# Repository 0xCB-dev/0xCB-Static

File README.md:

# 0xcb-static
## 40% with OLED and Encoder running QMK

Licence | OSHWA
:-------------------------:|:-------------------------:
 | 

#### Flashing

* `qmk clone`
* `cd qmk_firmware`
* `export LTO=Y`
* To go to bootloader hold the ESC key while plugging in (or RESET switch, then hold the BOOT switch, release RESET, release BOOT).
The board should now appear in lsusb (or device manager).
* `make 0xcb/static:via:flash`

### Assembly:

You can use the [humanpnp](https://files.0xcb.dev/0xCB-Static/humanpnp.html) to easily place components.

### PCB:
KiCad 6 stable

[Schematic](https://github.com/0xCB-dev/0xcb-static/blob/main/rev1.0/0xcb-static.pdf)

Top | Bottom
:-------------------------:|:-------------------------:
  |  

### 3D files:
[STLs](https://github.com/0xCB-dev/0xcb-static/tree/main/3D-files)

#### BOM:
| References     | Value          | Quantity |Part Nb.             |
|----------------|----------------|----------|---------------------|
| C3, C4         | 20pF           | 2        |C415398              |
| C1, C2         | 0.1uF          | 2        |C409821              |
| R1, R2         | 5.1K           | 2        |C58676               |
| R3, R4         | 75             | 2        |C713897              |
| R5             | 10k            | 1        |C58673               |
| R6             | 1.5k           | 1        |C433494              |
| D1, ..., D48   | 1N4148         | 48       |C14516               |
| D49, D50       | 1N4729         | 2        |C2532                |
| U1             | ATmega328-P    | 1        |ATMEGA328P-PU-ND     |
| Y1             | 16MHz          | 1        |C16212               |
| F1             | 500mA          | 1        |C268799              |
| SW1, SW2       | RESET, BOOT    | 1        |450-1650-ND          |
| MX1, ..., MX44 | MX-NoLED       | 43       |Cherry MX switches   |
| OL1            | OLED           | 1        |SSD1306 128x32       |
| MX12           | EC11           | 1        |PEC11R-4220F-S0024-ND|
| J1             | USB4085 Type C | 1        |640-USB4085-GF-A     |

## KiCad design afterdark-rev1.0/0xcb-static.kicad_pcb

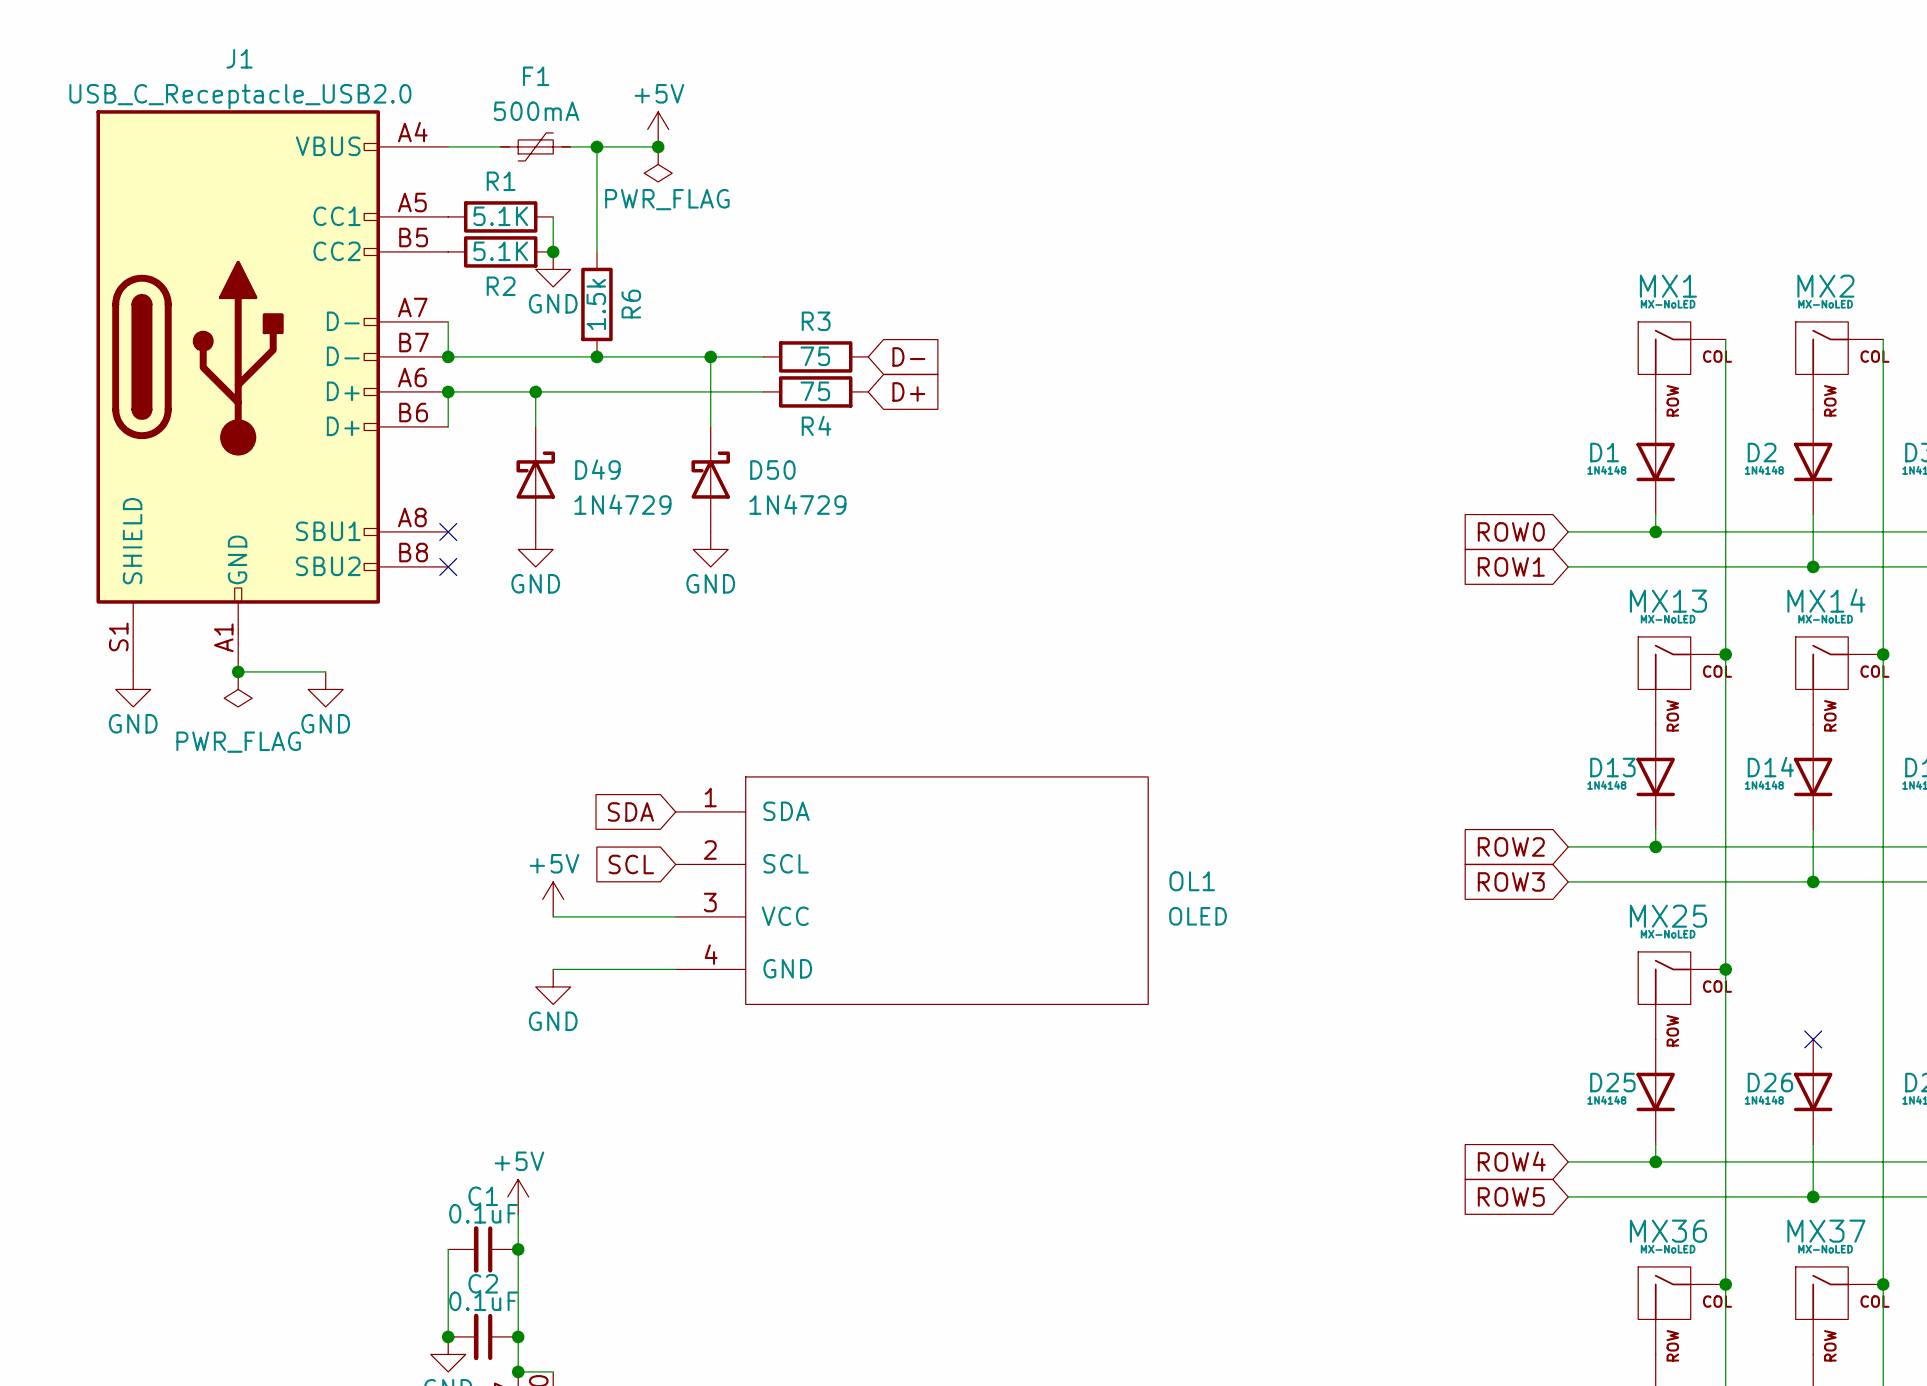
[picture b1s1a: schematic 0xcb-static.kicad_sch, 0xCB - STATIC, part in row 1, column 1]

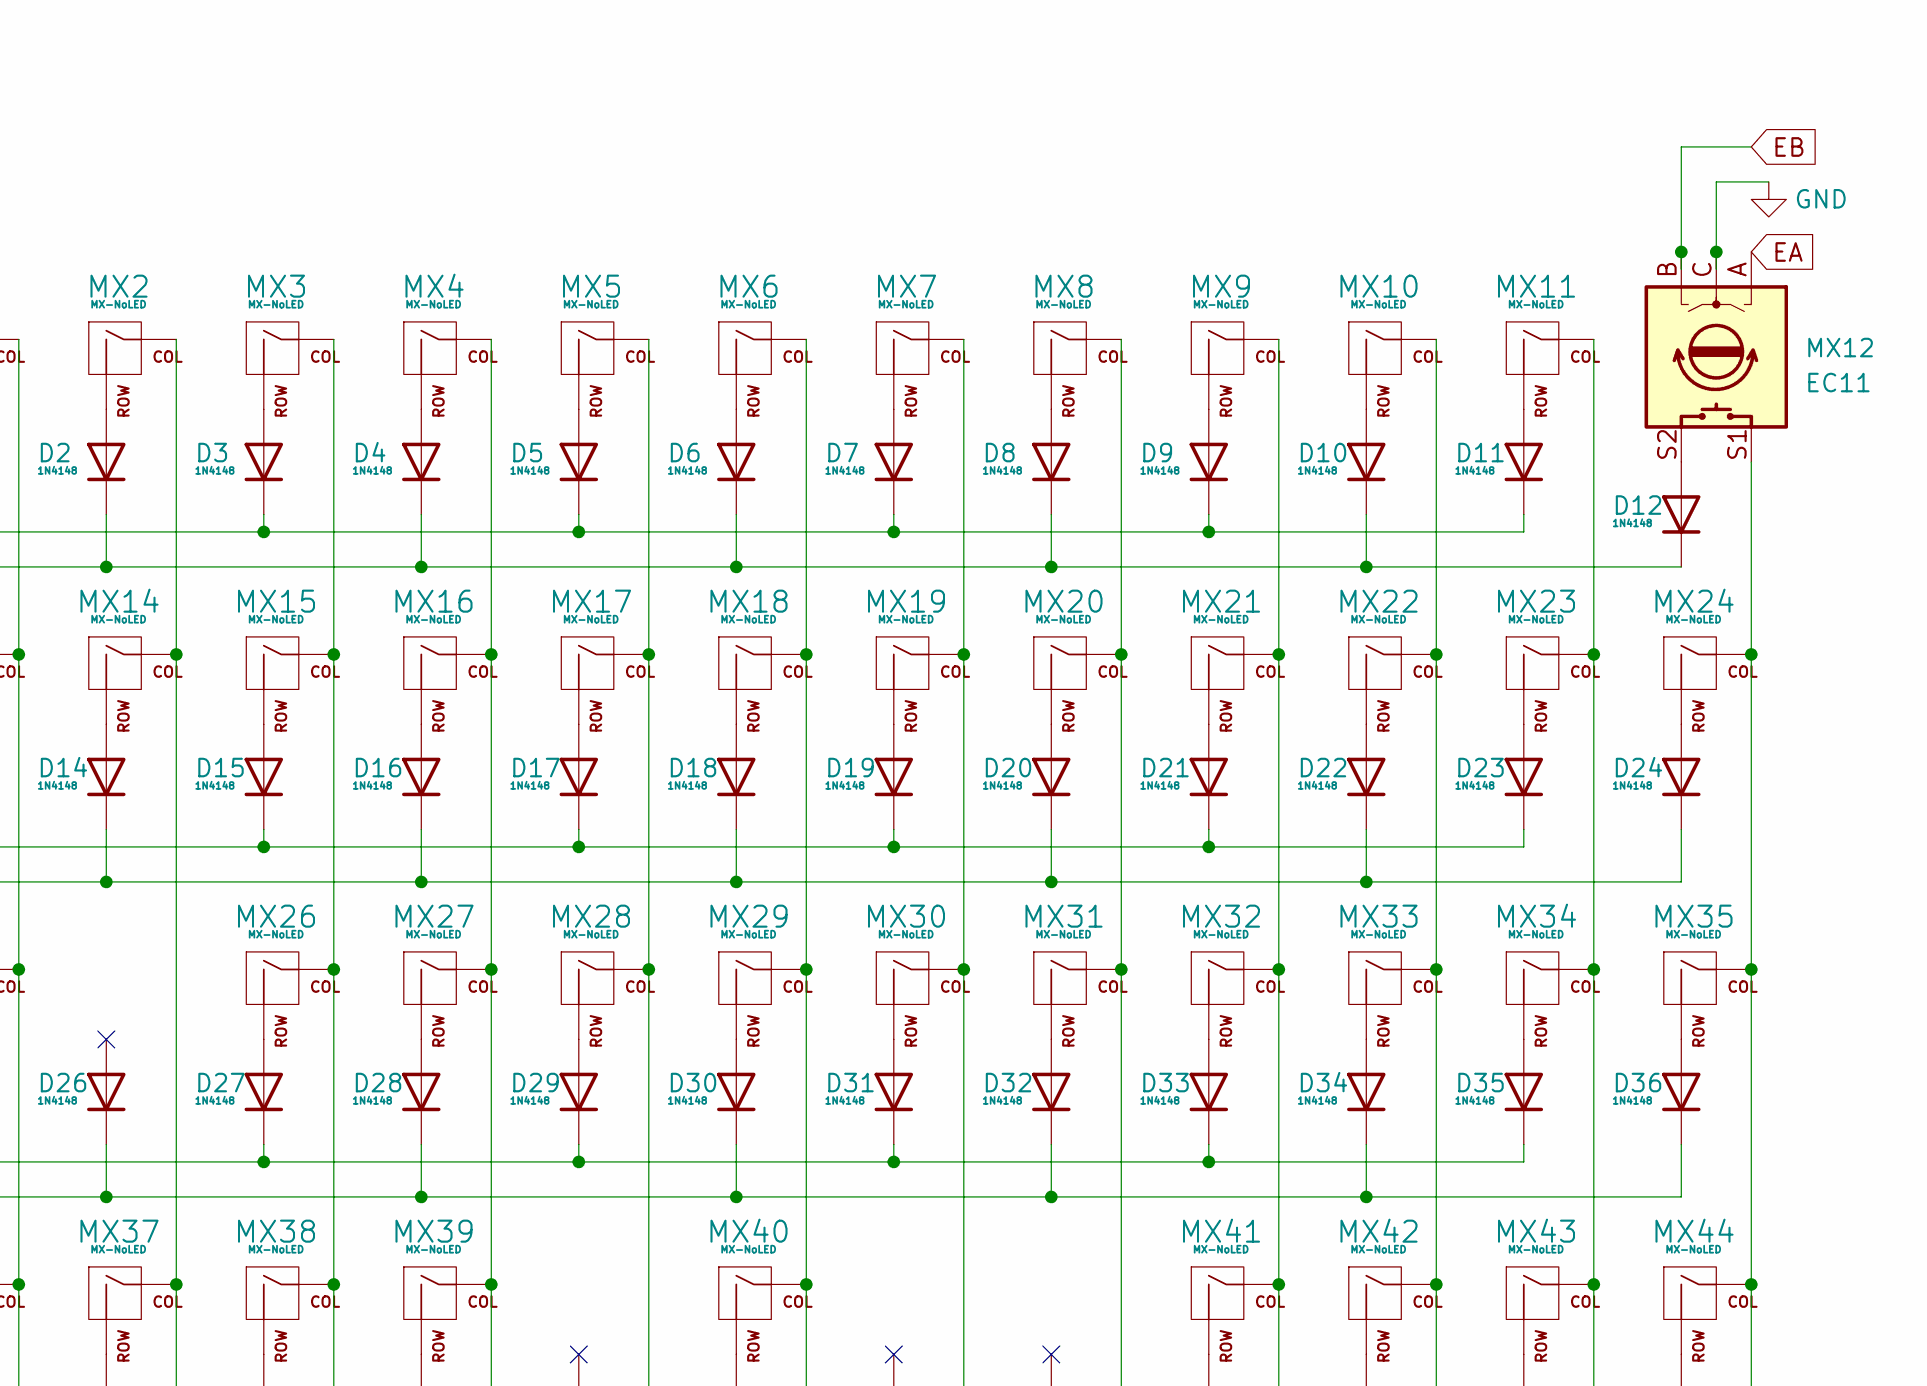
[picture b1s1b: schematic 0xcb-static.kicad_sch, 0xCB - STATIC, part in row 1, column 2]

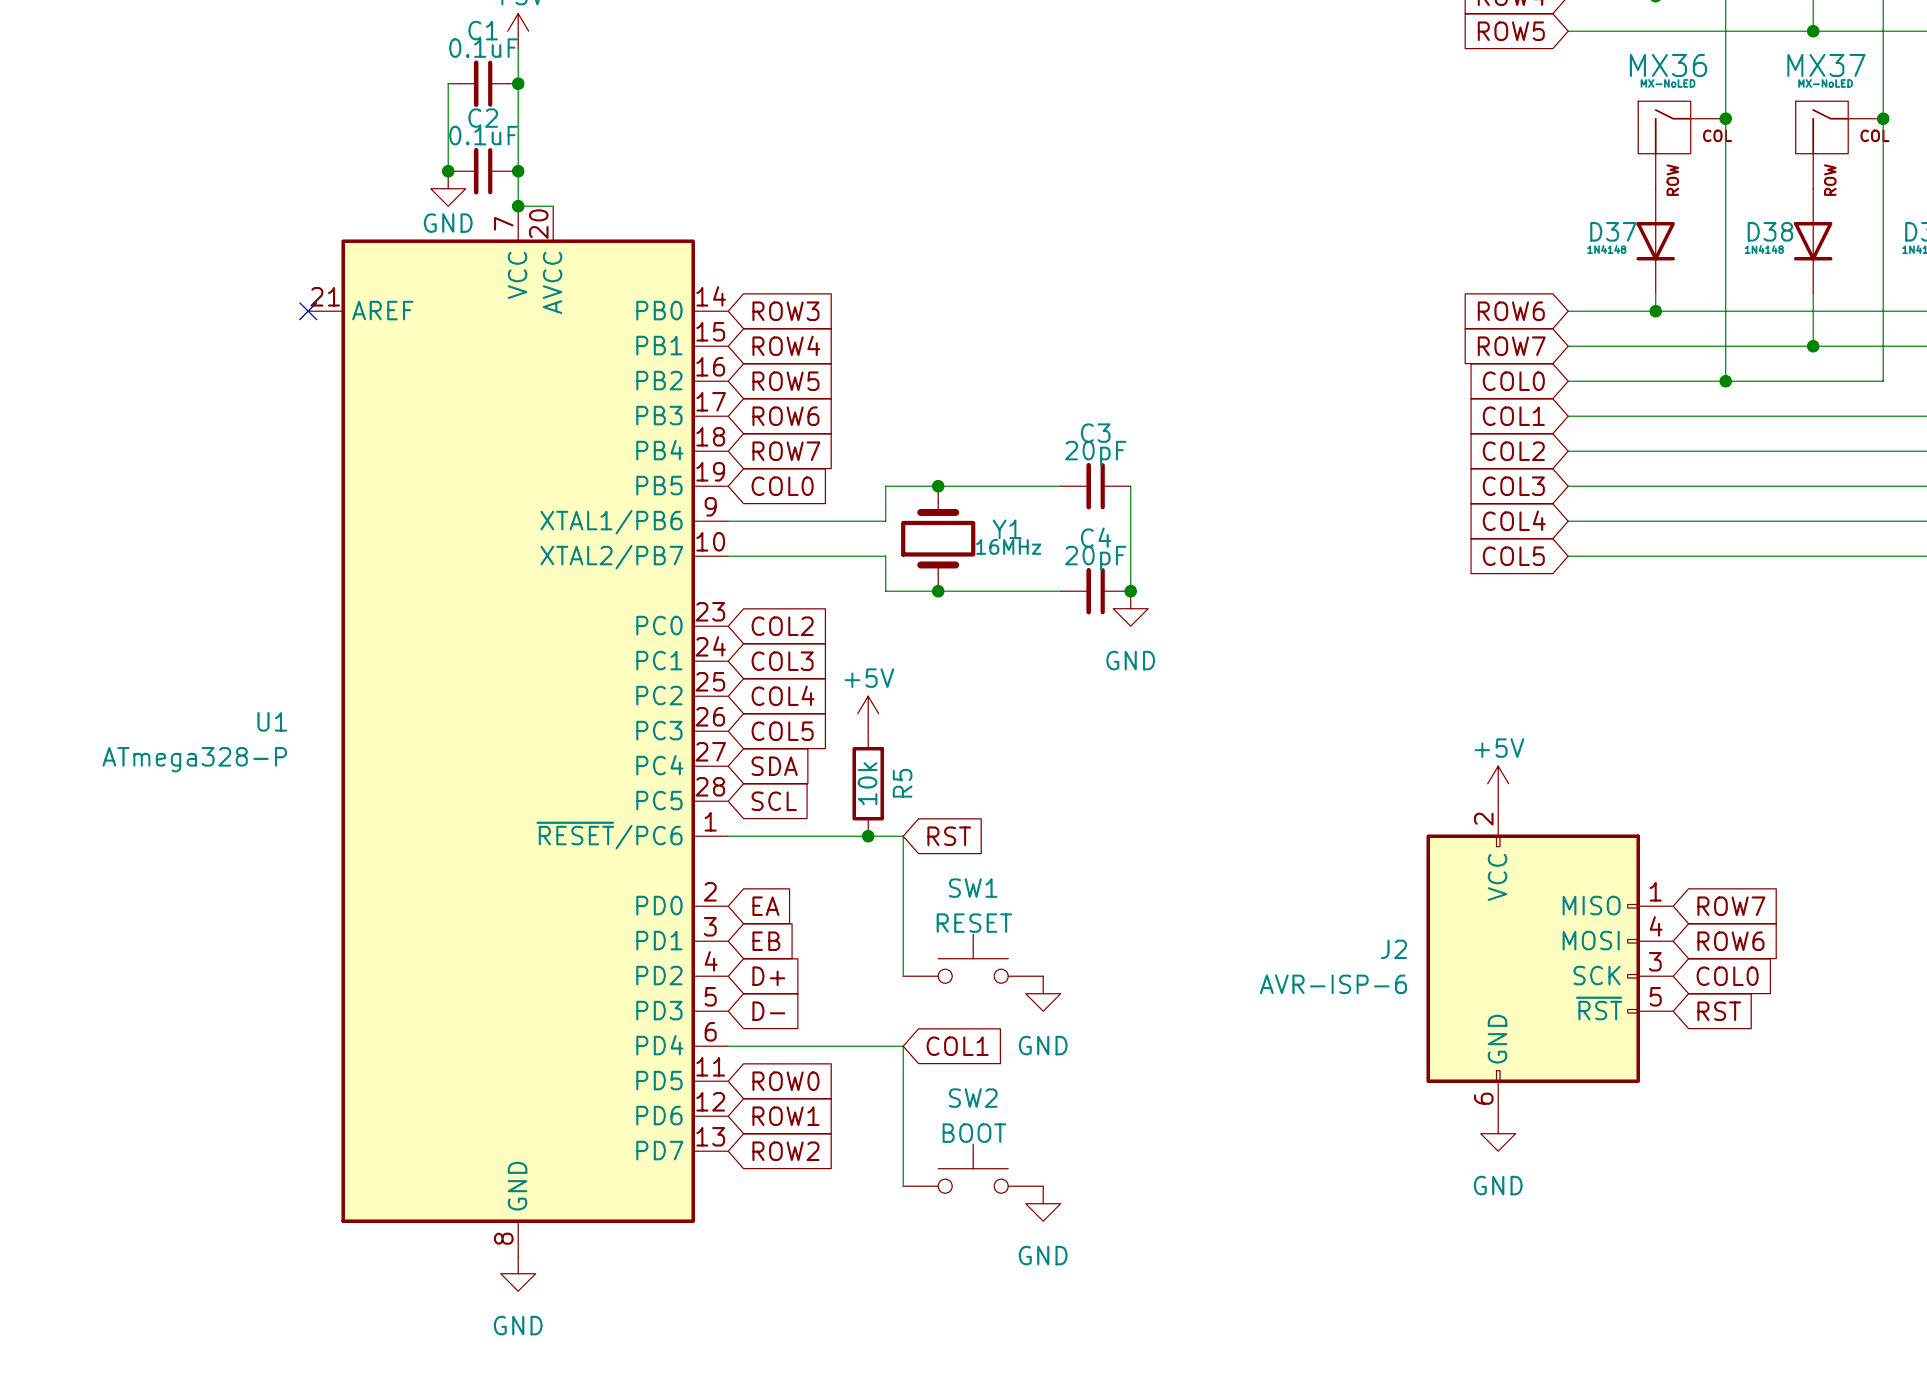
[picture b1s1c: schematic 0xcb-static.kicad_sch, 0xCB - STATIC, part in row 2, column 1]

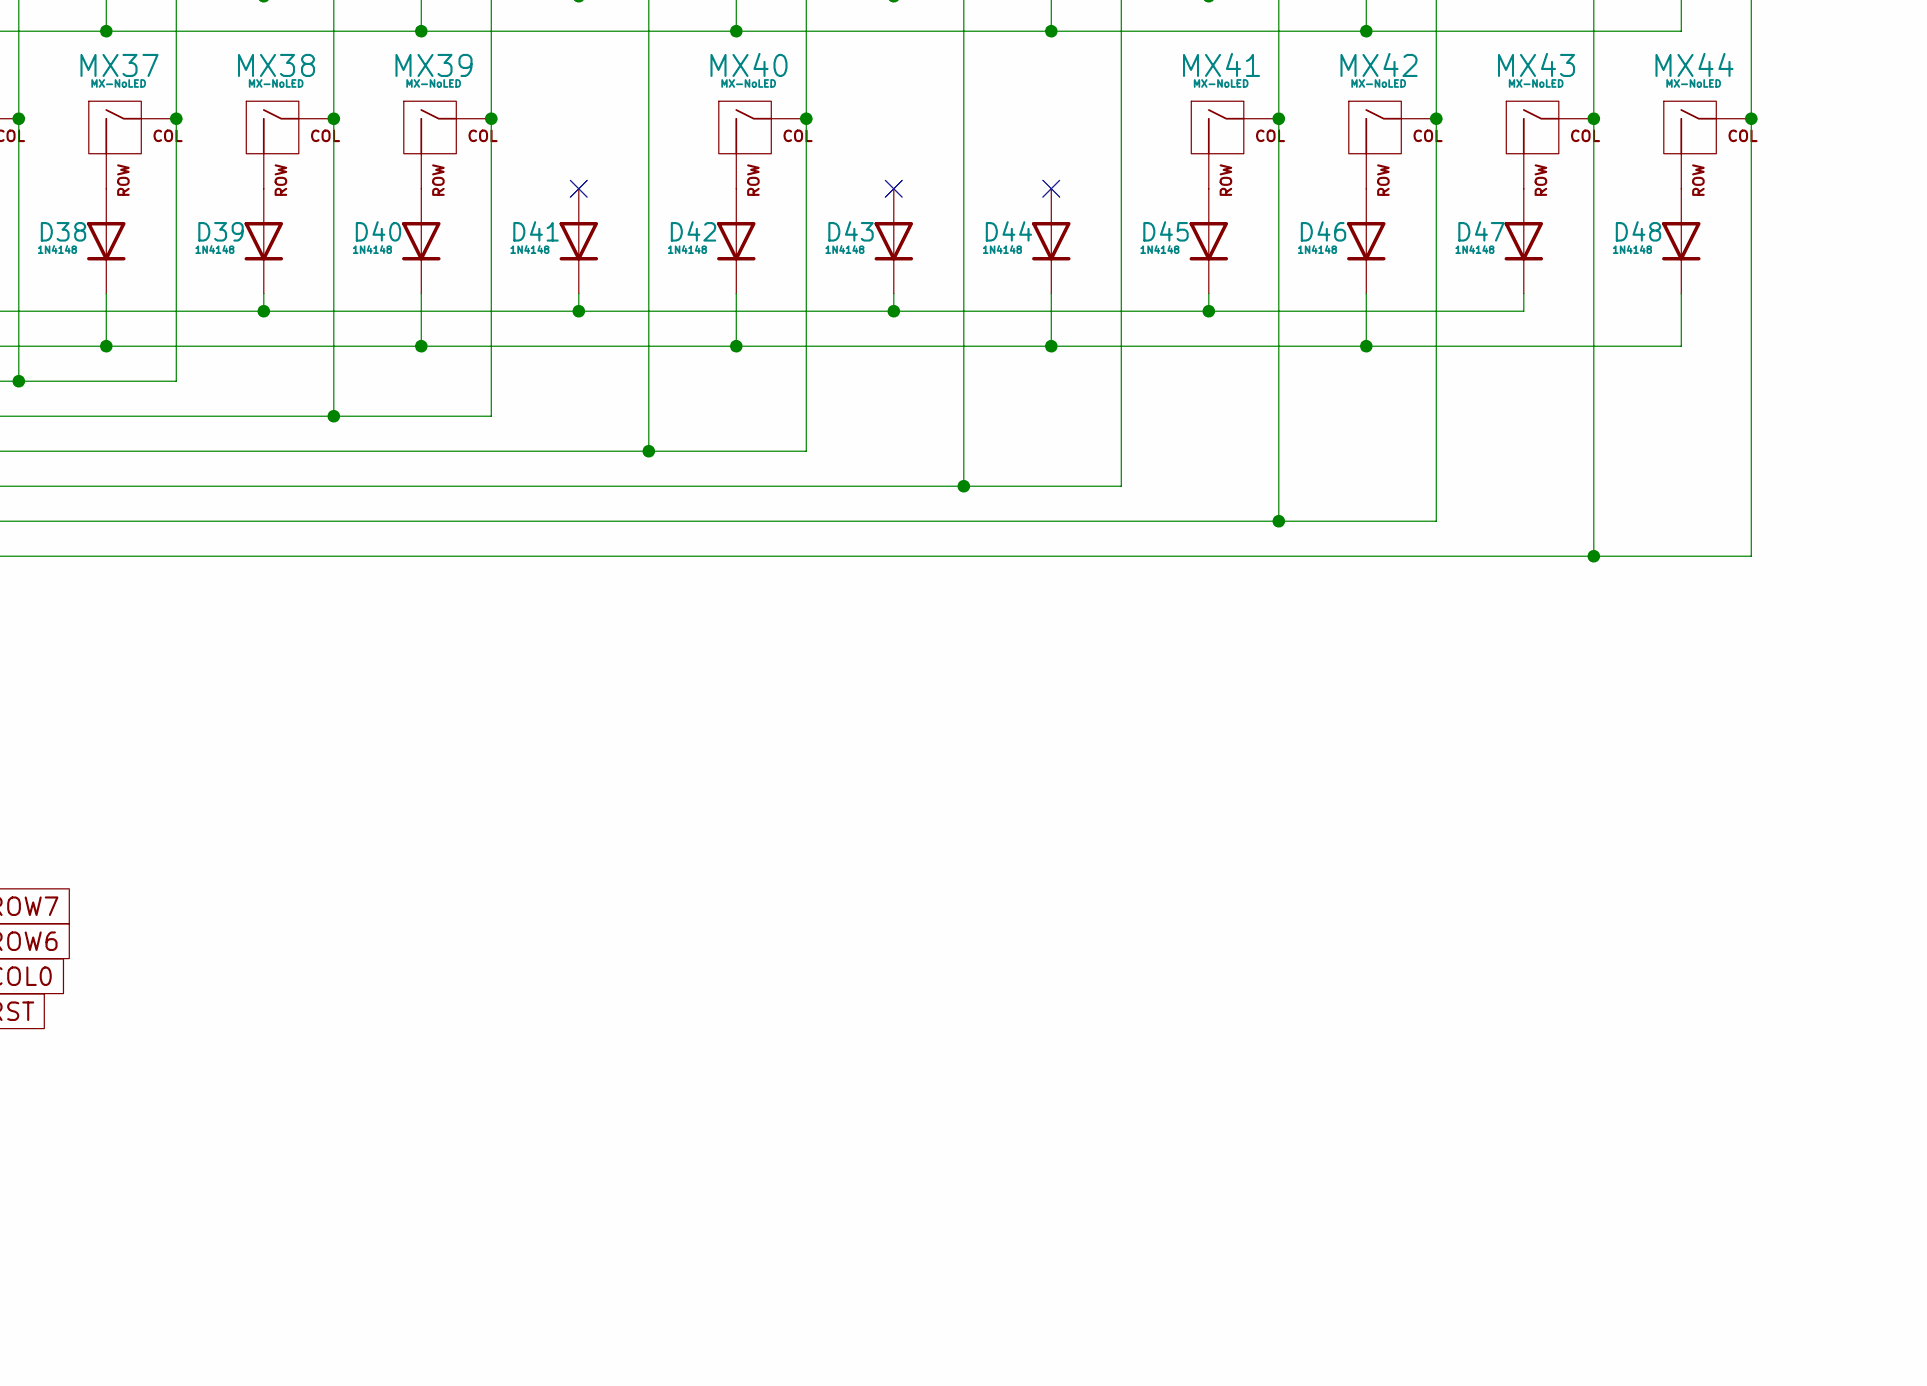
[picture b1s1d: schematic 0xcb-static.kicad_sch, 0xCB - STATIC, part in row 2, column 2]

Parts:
C1, C2: 0.1uF; C_Disc_D5.0mm_W2.5mm_P5.00mm; Part Nb. C277965
C3, C4: 20pF; C_Disc_D3.0mm_W1.6mm_P2.50mm; Part Nb. C254096
D1, D2, D3, D4, D5, D6, D7, D8, D9, D10, D11, D12, D13, D14, D15, D16, D17, D18, D19, D20, D21, D22, D23, D24, D25, D26, D27, D28, D29, D30, D31, D32, D33, D34, D35, D36, D37, D38, D39, D40, D41, D42, D43, D44, D45, D46, D47, D48: 1N4148; D_DO-35_SOD27_P12.70mm_Horizontal; Part Nb. C14538
D49, D50: 1N4729; D_DO-41_SOD81_P7.62mm_Horizontal; Part Nb. C2532
F1: 500mA; Fuse_BelFuse_0ZRE0025FF_L9.6mm_W3.8mm; Part Nb. C268799
J1: USB_C_Receptacle_USB2.0; USB_C_Receptacle_GCT_USB4085; Part Nb. 2073-USB4085-GF-ACT-ND
J2: AVR-ISP-6; PinHeader_2x03_P2.54mm_Vertical
MX1, MX2, MX3, MX4, MX5, MX6, MX7, MX8, MX9, MX10, MX11, MX14, MX15, MX16, MX17, MX18, MX19, MX20, MX21, MX22, MX24, MX26, MX27, MX28, MX29, MX30, MX31, MX32, MX33, MX34, MX36, MX37, MX38, MX40, MX42, MX43, MX44: MX-NoLED; MXOnly-1U-NoLED; Part Nb. amz
MX12: EC11; RotaryEncoder_Alps_EC11E-Switch_Vertical_H20mm; Part Nb. amz
MX13, MX35: MX-NoLED; MXOnly-1.25U-NoLED; Part Nb. amz
MX23, MX25: MX-NoLED; MXOnly-1.75U-NoLED; Part Nb. amz
MX39: MX-NoLED; MXOnly-2.75U-NoLED; Part Nb. amz
MX41: MX-NoLED; MXOnly-2.25U-NoLED; Part Nb. amz
OL1: OLED; PinSocket_1x04_P2.54mm_Vertical; Part Nb. amz
R1, R2: 5.1K; R_Axial_DIN0204_L3.6mm_D1.6mm_P5.08mm_Horizontal; Part Nb. C58676
R3, R4: 75; R_Axial_DIN0204_L3.6mm_D1.6mm_P5.08mm_Horizontal; Part Nb. C713897
R5: 10k; R_Axial_DIN0204_L3.6mm_D1.6mm_P5.08mm_Horizontal; Part Nb. C58673
R6: 1.5k; R_Axial_DIN0204_L3.6mm_D1.6mm_P5.08mm_Horizontal; Part Nb. C433494
SW1: RESET; SW_PUSH_6mm_H5mm; Part Nb. C127509
SW2: BOOT; SW_PUSH_6mm_H5mm; Part Nb. C127509
U1: ATmega328-P; DIP-28_W7.62mm; Part Nb. C613508
Y1: 16MHz; Crystal_HC49-4H_Vertical; Part Nb. C16212

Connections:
+5V: C1.1, C2.1, F1.2, J2.2 (VCC), OL1.3 (VCC), R5.2, R6.1, U1.7 (VCC), U1.20 (AVCC)
COL0: J2.3 (SCK), MX1.1 (COL), MX2.1 (COL), MX13.1 (COL), MX14.1 (COL), MX25.1 (COL), MX36.1 (COL), MX37.1 (COL), U1.19 (PB5); also elsewhere on the board
COL1: MX3.1 (COL), MX4.1 (COL), MX15.1 (COL), MX16.1 (COL), MX26.1 (COL), MX27.1 (COL), MX38.1 (COL), MX39.1 (COL), SW2.1, U1.6 (PD4); also elsewhere on the board
COL2: MX5.1 (COL), MX6.1 (COL), MX17.1 (COL), MX18.1 (COL), MX28.1 (COL), MX29.1 (COL), MX40.1 (COL), U1.23 (PC0); also elsewhere on the board
COL3: MX7.1 (COL), MX8.1 (COL), MX19.1 (COL), MX20.1 (COL), MX30.1 (COL), MX31.1 (COL), U1.24 (PC1)
COL4: MX9.1 (COL), MX10.1 (COL), MX21.1 (COL), MX22.1 (COL), MX32.1 (COL), MX33.1 (COL), MX41.1 (COL), MX42.1 (COL), U1.25 (PC2); also elsewhere on the board
COL5: MX11.1 (COL), MX12.S1, MX23.1 (COL), MX24.1 (COL), MX34.1 (COL), MX35.1 (COL), MX43.1 (COL), MX44.1 (COL), U1.26 (PC3); also elsewhere on the board
D+: R4.2, U1.4 (PD2)
D-: R3.1, U1.5 (PD3)
EA: MX12.A, U1.2 (PD0)
EB: MX12.B, U1.3 (PD1)
GND: C1.2, C2.2, C3.1, C4.1, D49.2 (A), D50.2 (A), J1.A1 (GND), J1.A12 (GND), J1.B1 (GND), J1.B12 (GND), J1.S1 (SHIELD), J2.6 (GND), MX12.C, OL1.4 (GND), R1.1, R2.2, SW1.2, SW2.2, U1.8 (GND), U1.22 (GND)
unnamed: C3.2, U1.9 (XTAL1/PB6), Y1.2
unnamed: C4.2, U1.10 (XTAL2/PB7), Y1.1
unnamed: D1.2 (A), MX1.2 (ROW)
unnamed: D2.2 (A), MX2.2 (ROW)
unnamed: D3.2 (A), MX3.2 (ROW)
unnamed: D4.2 (A), MX4.2 (ROW)
unnamed: D5.2 (A), MX5.2 (ROW)
unnamed: D6.2 (A), MX6.2 (ROW)
unnamed: D7.2 (A), MX7.2 (ROW)
unnamed: D8.2 (A), MX8.2 (ROW)
unnamed: D9.2 (A), MX9.2 (ROW)
unnamed: D10.2 (A), MX10.2 (ROW)
unnamed: D11.2 (A), MX11.2 (ROW)
unnamed: D12.2 (A), MX12.S2
unnamed: D13.2 (A), MX13.2 (ROW)
unnamed: D14.2 (A), MX14.2 (ROW)
unnamed: D15.2 (A), MX15.2 (ROW)
unnamed: D16.2 (A), MX16.2 (ROW)
unnamed: D17.2 (A), MX17.2 (ROW)
unnamed: D18.2 (A), MX18.2 (ROW)
unnamed: D19.2 (A), MX19.2 (ROW)
unnamed: D20.2 (A), MX20.2 (ROW)
unnamed: D21.2 (A), MX21.2 (ROW)
unnamed: D22.2 (A), MX22.2 (ROW)
unnamed: D23.2 (A), MX23.2 (ROW)
unnamed: D24.2 (A), MX24.2 (ROW)
unnamed: D25.2 (A), MX25.2 (ROW)
unnamed: D27.2 (A), MX26.2 (ROW)
unnamed: D28.2 (A), MX27.2 (ROW)
unnamed: D29.2 (A), MX28.2 (ROW)
unnamed: D30.2 (A), MX29.2 (ROW)
unnamed: D31.2 (A), MX30.2 (ROW)
unnamed: D32.2 (A), MX31.2 (ROW)
unnamed: D33.2 (A), MX32.2 (ROW)
unnamed: D34.2 (A), MX33.2 (ROW)
unnamed: D35.2 (A), MX34.2 (ROW)
unnamed: D36.2 (A), MX35.2 (ROW)
unnamed 49: D37.2 (A), MX36.2 (ROW); also elsewhere on the board
unnamed 50: D38.2 (A), MX37.2 (ROW); also elsewhere on the board
unnamed 51: D39.2 (A), MX38.2 (ROW); also elsewhere on the board
unnamed 52: D40.2 (A), MX39.2 (ROW); also elsewhere on the board
unnamed 54: D42.2 (A), MX40.2 (ROW); also elsewhere on the board
unnamed: D45.2 (A), MX41.2 (ROW)
unnamed: D46.2 (A), MX42.2 (ROW)
unnamed 57: D47.2 (A), MX43.2 (ROW); also elsewhere on the board
unnamed 58: D48.2 (A), MX44.2 (ROW); also elsewhere on the board
unnamed: D49.1 (K), J1.A6 (D+), J1.B6 (D+), R4.1
unnamed: D50.1 (K), J1.A7 (D-), J1.B7 (D-), R3.2, R6.2
unnamed: F1.1, J1.A4 (VBUS), J1.A9 (VBUS), J1.B4 (VBUS), J1.B9 (VBUS)
unnamed: J1.A5 (CC1), R1.2
unnamed: J1.B5 (CC2), R2.1
ROW0: D1.1 (K), D3.1 (K), D5.1 (K), D7.1 (K), D9.1 (K), D11.1 (K), U1.11 (PD5)
ROW1: D2.1 (K), D4.1 (K), D6.1 (K), D8.1 (K), D10.1 (K), D12.1 (K), U1.12 (PD6)
ROW2: D13.1 (K), D15.1 (K), D17.1 (K), D19.1 (K), D21.1 (K), D23.1 (K), U1.13 (PD7)
ROW3: D14.1 (K), D16.1 (K), D18.1 (K), D20.1 (K), D22.1 (K), D24.1 (K), U1.14 (PB0)
ROW4: D25.1 (K), D27.1 (K), D29.1 (K), D31.1 (K), D33.1 (K), D35.1 (K), U1.15 (PB1)
ROW5: D26.1 (K), D28.1 (K), D30.1 (K), D32.1 (K), D34.1 (K), D36.1 (K), U1.16 (PB2)
ROW6: D37.1 (K), D39.1 (K), D41.1 (K), D43.1 (K), D45.1 (K), D47.1 (K), J2.4 (MOSI), U1.17 (PB3)
ROW7: D38.1 (K), D40.1 (K), D42.1 (K), D44.1 (K), D46.1 (K), D48.1 (K), J2.1 (MISO), U1.18 (PB4)
RST: J2.5 (~RST), R5.1, SW1.1, U1.1 (~RESET~/PC6)
SCL: OL1.2 (SCL), U1.28 (PC5)
SDA: OL1.1 (SDA), U1.27 (PC4)

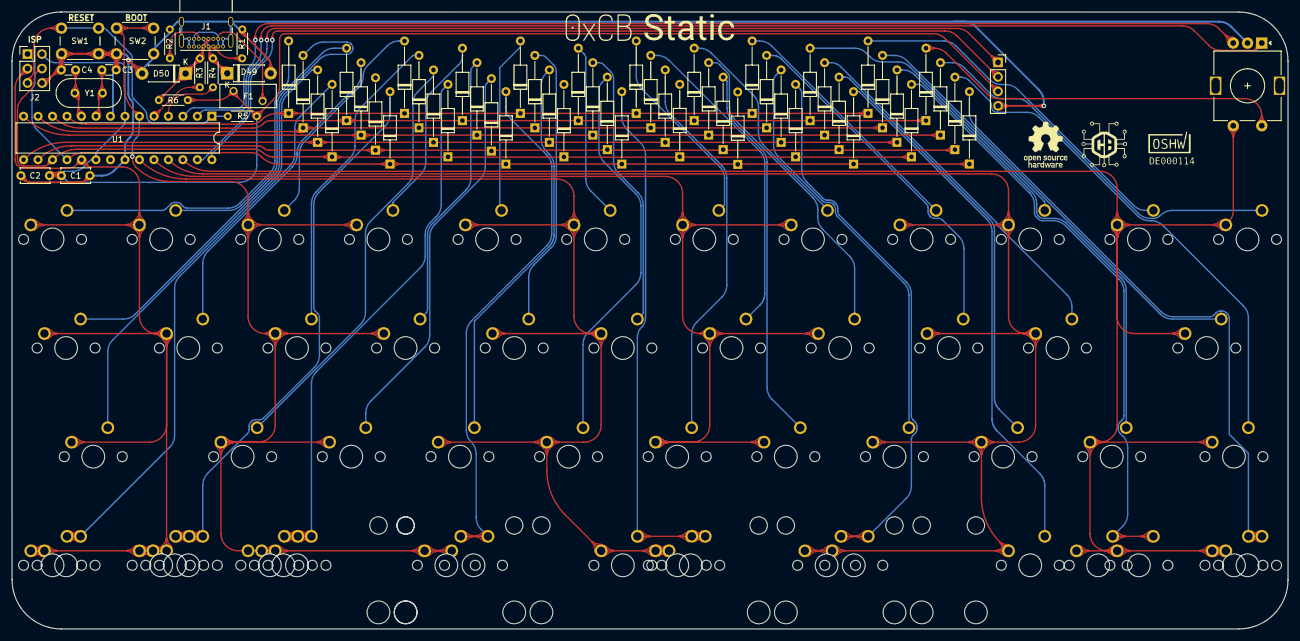
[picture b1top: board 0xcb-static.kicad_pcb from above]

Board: 2 copper layers, 223.8 x 108.2 mm, 127 parts (0 on the bottom side), 74 nets.

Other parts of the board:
L1: font1; svg2mod
L2: font2; svg2mod
L3: OSHW-Logo_7.5x8mm_SilkScreen
L4: LOGO; logo
MX36_1, MX37_1, MX38_1, MX43_1, MX44_1: MX-NoLED; MXOnly-1.25U-NoLED
MX37_2, MX38_2, MX40_1: MX-NoLED; MXOnly-1U-NoLED
MX39_1: MX-NoLED; MXOnly-2.25U-NoLED
MX40_2: 6.25U; MXOnly-6.25U-NoLED
MX41_1: MX-NoLED; MXOnly-2.75U-NoLED

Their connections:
COL0: MX36_1.1 (COL), MX37_1.1 (COL), MX37_2.1 (COL); also elsewhere on the board
COL1: MX38_1.1 (COL), MX38_2.1 (COL), MX39_1.1 (COL); also elsewhere on the board
COL2: MX40_1.1 (COL), MX40_2.1; also elsewhere on the board
COL4: MX41_1.1 (COL); also elsewhere on the board
COL5: MX43_1.1 (COL), MX44_1.1 (COL); also elsewhere on the board
unnamed 49: MX36_1.2 (ROW); also elsewhere on the board
unnamed 50: MX37_1.2 (ROW), MX37_2.2 (ROW); also elsewhere on the board
unnamed 51: MX38_1.2 (ROW), MX38_2.2 (ROW); also elsewhere on the board
unnamed 52: MX39_1.2 (ROW); also elsewhere on the board
unnamed 54: MX40_1.2 (ROW), MX40_2.2; also elsewhere on the board
unnamed 57: MX43_1.2 (ROW); also elsewhere on the board
unnamed 58: MX44_1.2 (ROW); also elsewhere on the board

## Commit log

2021-05-10 added submodules
2021-05-10 added libs
2021-05-28 v1-proto
2021-05-28 added v1
2021-05-30 added readme
2021-05-30 updated bom
2021-06-26 updated prod files
2021-06-26 updated readme bom
2022-01-08 removed zips
2022-01-08 added gitignore
2022-01-18 updated ibom link
2022-01-25 made a version for use with afterdark with rounded traces and no ground plane
2022-07-02 removed case sensitive files for windows ._.
2022-07-02 added acrylic case files
